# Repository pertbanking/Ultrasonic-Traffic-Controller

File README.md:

# Ultrasonic-Traffic-Controller
The Gay Atheist Club's Embedded System project repository.

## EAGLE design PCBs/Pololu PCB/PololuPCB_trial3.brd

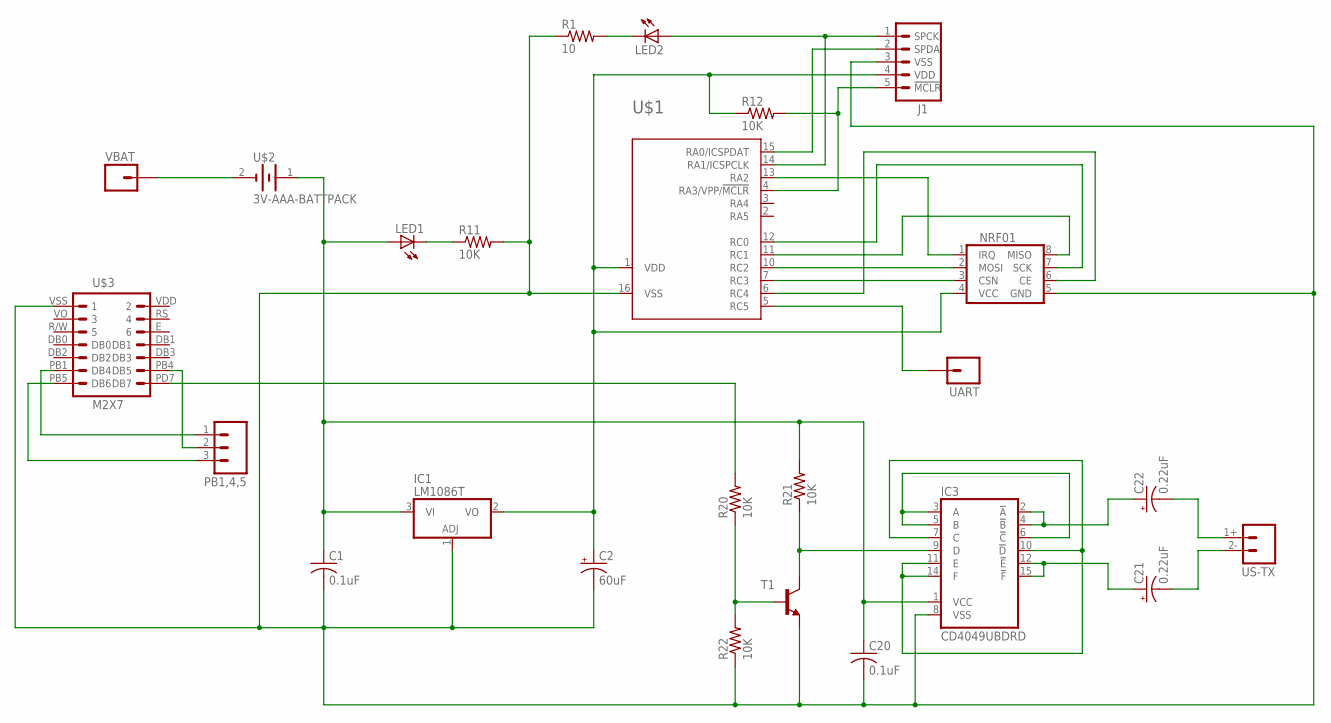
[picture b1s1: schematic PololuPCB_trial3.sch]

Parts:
C1, C20: 0.1uF; C0805
C2: 60uF; E2,5-5
C21, C22: 0.22uF; E2,5-6E
IC1: LM1086T; TO220H
IC3: CD4049UBDRD; SO16
J1: M05PTH; 1X05
LED1: LED5MM
LED2: LED_E; LED_1206
NRF01: NRF01; JP4Q
PB1,4,5: M03PTH; 1X03
R1: 10; R0805
R11, R12, R20, R21, R22: 10K; R0805
T1: -NPN-SOT23-EBC; SOT23-EBC
U$1: PIC16F1503(DIL16); DIL16
U$2: 3V-AAA-BATTPACK
U$3: M2X7; 2X07
UART: M01PTH_LONGPAD; 1X01_LONGPAD
US-TX: M02UT-1640K-TT-2-R; ULTRASONIC-PEIZO
VBAT: M01PTH_LONGPAD; 1X01_LONGPAD

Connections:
unnamed: IC3.9 (D), R21.1, T1.C
unnamed: R20.2, U$3.PD7 (DB7)
unnamed: IC3.7 (C), IC3.10 (!D), IC3.11 (E), IC3.14 (F)
unnamed: IC3.3 (A), IC3.5 (B), IC3.6 (!C)
unnamed: C22.+, IC3.2 (!A), IC3.4 (!B)
unnamed: C1.2, C2.-, C20.2, IC1.1 (ADJ), IC3.8 (VSS), J1.3 (VSS), NRF01.5 (GND), R1.1, R11.2, R22.1, T1.E, U$1.16 (VSS), U$3.VSS (1)
unnamed: C21.+, IC3.12 (!E), IC3.15 (!F)
unnamed: R20.1, R22.2, T1.B
unnamed: C2.+, IC1.2 (VO), J1.4 (VDD), NRF01.4 (VCC), R12.1, U$1.1 (VDD)
unnamed: LED2.C, R1.2
unnamed: NRF01.1 (IRQ), U$1.13 (RA2)
unnamed: NRF01.8 (MISO), U$1.11 (RC1)
unnamed: NRF01.3 (CSN), U$1.7 (RC3)
unnamed: NRF01.6 (CE), U$1.6 (RC4)
unnamed: NRF01.2 (MOSI), U$1.10 (RC2)
unnamed: NRF01.7 (SCK), U$1.12 (RC0)
unnamed: J1.2 (SPDA), U$1.15 (RA0/ICSPDAT)
unnamed: J1.1 (SPCK), LED2.A, U$1.14 (RA1/ICSPCLK)
unnamed: J1.5 (!MCLR), R12.2, U$1.4 (RA3/VPP/!MCLR)
unnamed: LED1.K (C), R11.1
unnamed: C22.-, US-TX.1+ (1)
unnamed: C21.-, US-TX.2- (2)
unnamed: C1.1, C20.1, IC1.3 (VI), IC3.1 (VCC), LED1.A, R21.2, U$2.1 (+)
unnamed: U$2.2 (-), VBAT.1
unnamed: U$1.5 (RC5), UART.1
unnamed: PB1,4,5.2, U$3.PB4 (DB5)
unnamed: PB1,4,5.1, U$3.PB1 (DB4)
unnamed: PB1,4,5.3, U$3.PB5 (DB6)

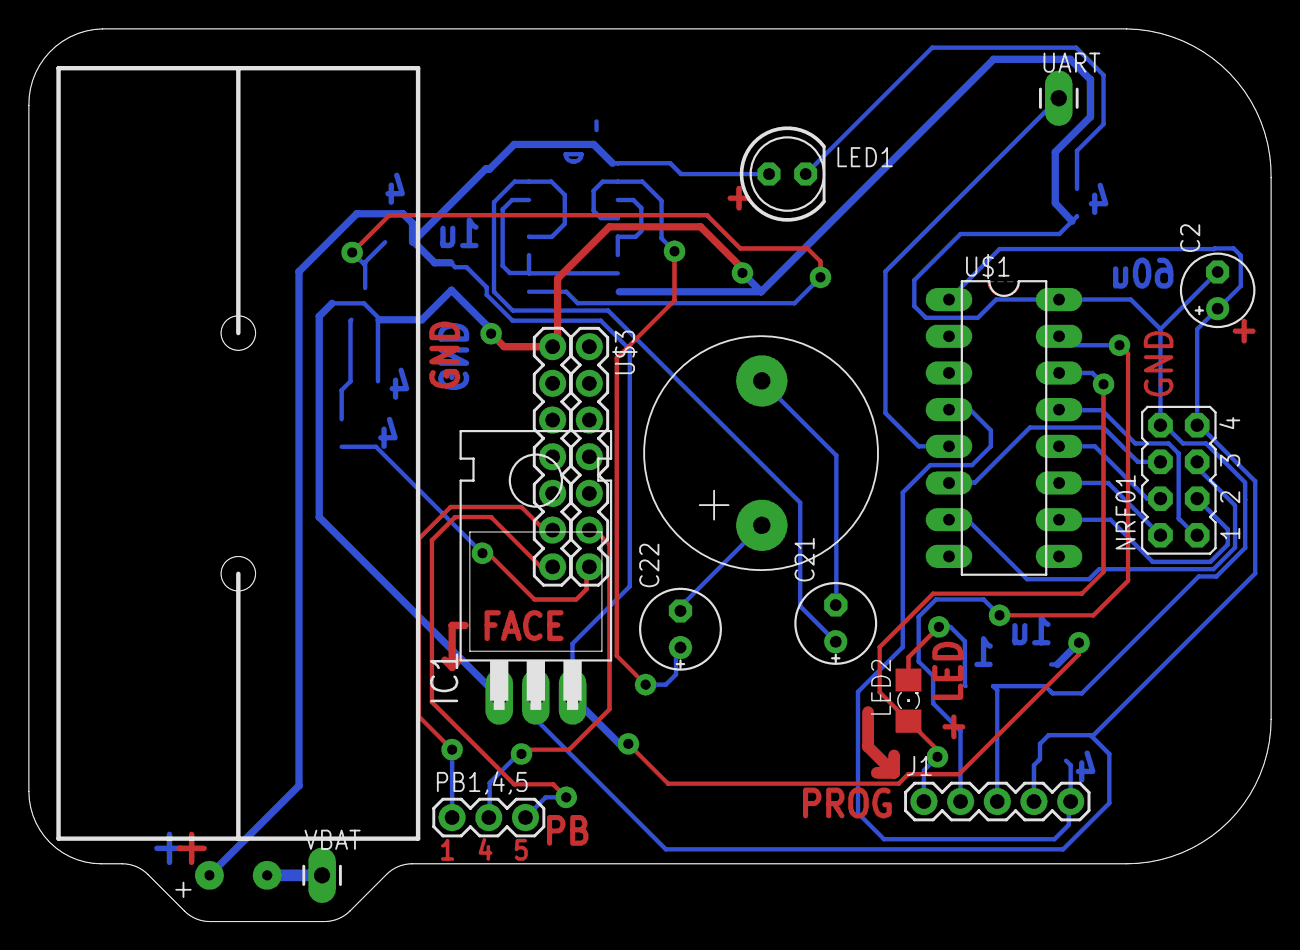
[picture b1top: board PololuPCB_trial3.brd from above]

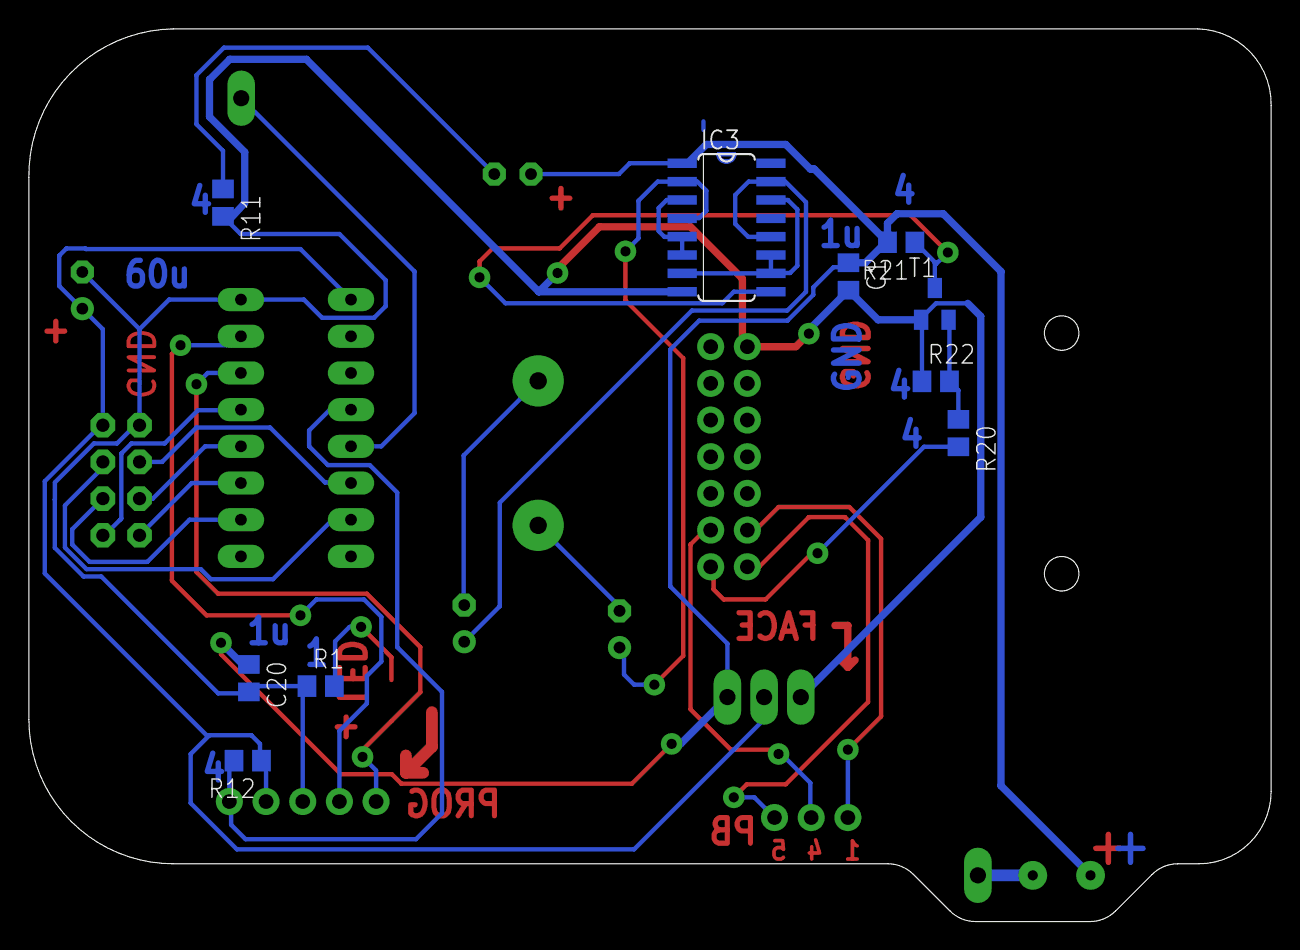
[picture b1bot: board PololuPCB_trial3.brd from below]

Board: 2 copper layers, 86.0 x 61.8 mm, 25 parts (10 on the bottom side), 28 nets.

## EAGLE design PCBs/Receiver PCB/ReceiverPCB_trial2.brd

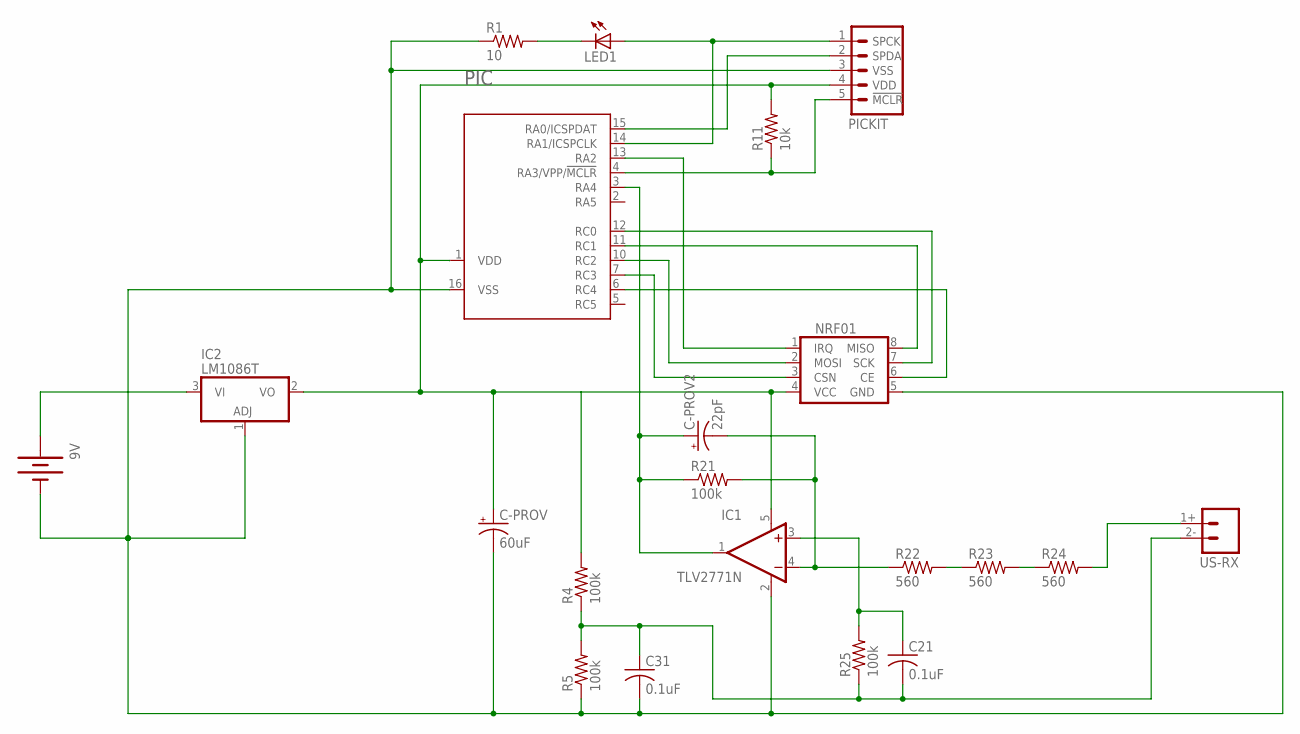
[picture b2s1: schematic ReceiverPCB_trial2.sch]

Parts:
9V: BATTERY9V; BATTCON_9V
C21, C31: 0.1uF; C0805
C-PROV: 60uF; E2,5-6E
C-PROV2: 22pF; E2,5-6E
IC1: TLV2771N; SOT23-5
IC2: LM1086T; TO220H
LED1: LED_E; LED_1206
NRF01: NRF01; JP4Q
PIC: PIC16F1503(DIL16); DIL16
PICKIT: M05PTH; 1X05
R1: 10; R0805
R4, R5, R21, R25: 100k; R0805
R11: 10k; R0805
R22, R23, R24: 560; R0805
US-RX: M02UT-1640K-TT-2-R; ULTRASONIC-PEIZO

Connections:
unnamed: LED1.A, PIC.14 (RA1/ICSPCLK), PICKIT.1 (SPCK)
unnamed: PIC.15 (RA0/ICSPDAT), PICKIT.2 (SPDA)
unnamed: LED1.C, R1.2
unnamed: C-PROV.+, IC1.5 (V+), IC2.2 (VO), NRF01.4 (VCC), PIC.1 (VDD), PICKIT.4 (VDD), R4.2, R11.2
unnamed: NRF01.1 (IRQ), PIC.13 (RA2)
unnamed: PIC.4 (RA3/VPP/!MCLR), PICKIT.5 (!MCLR), R11.1
unnamed: NRF01.8 (MISO), PIC.11 (RC1)
unnamed: NRF01.3 (CSN), PIC.7 (RC3)
unnamed: NRF01.2 (MOSI), PIC.10 (RC2)
unnamed: NRF01.7 (SCK), PIC.12 (RC0)
unnamed: NRF01.6 (CE), PIC.6 (RC4)
unnamed: 9V.-, C31.2, C-PROV.-, IC1.2 (V-), IC2.1 (ADJ), NRF01.5 (GND), PIC.16 (VSS), PICKIT.3 (VSS), R1.1, R5.1
unnamed: 9V.+, IC2.3 (VI)
unnamed: C-PROV2.+, IC1.1 (OUT), PIC.3 (RA4), R21.1
unnamed: R24.2, US-RX.1+ (1)
unnamed: R22.2, R23.1
unnamed: R23.2, R24.1
unnamed: C-PROV2.-, IC1.4 (-IN), R21.2, R22.1
unnamed: C21.2, C31.1, R4.1, R5.2, R25.1, US-RX.2- (2)
unnamed: C21.1, IC1.3 (+IN), R25.2

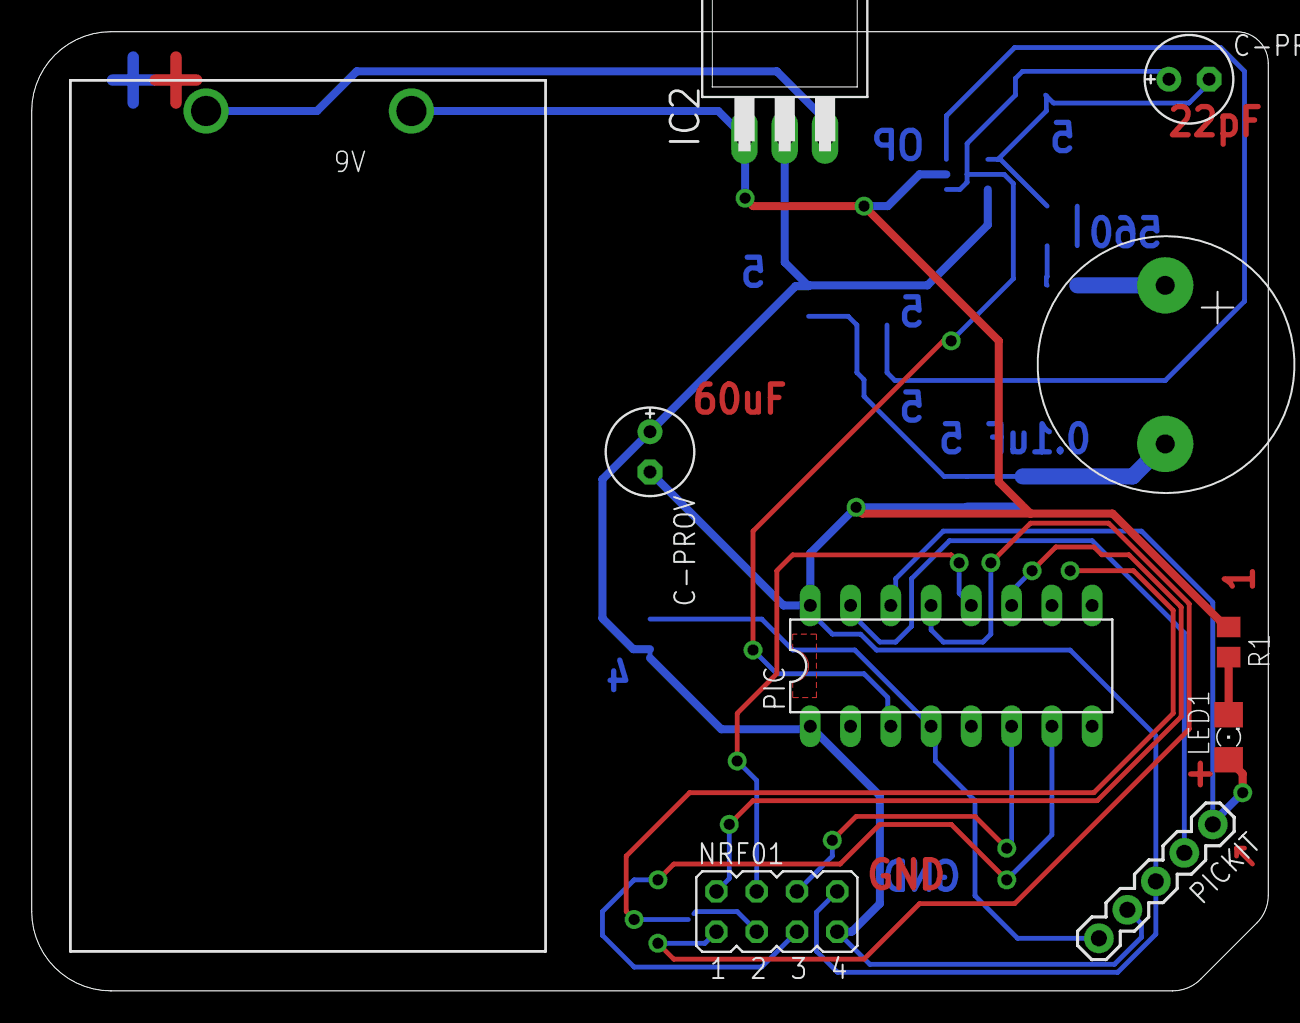
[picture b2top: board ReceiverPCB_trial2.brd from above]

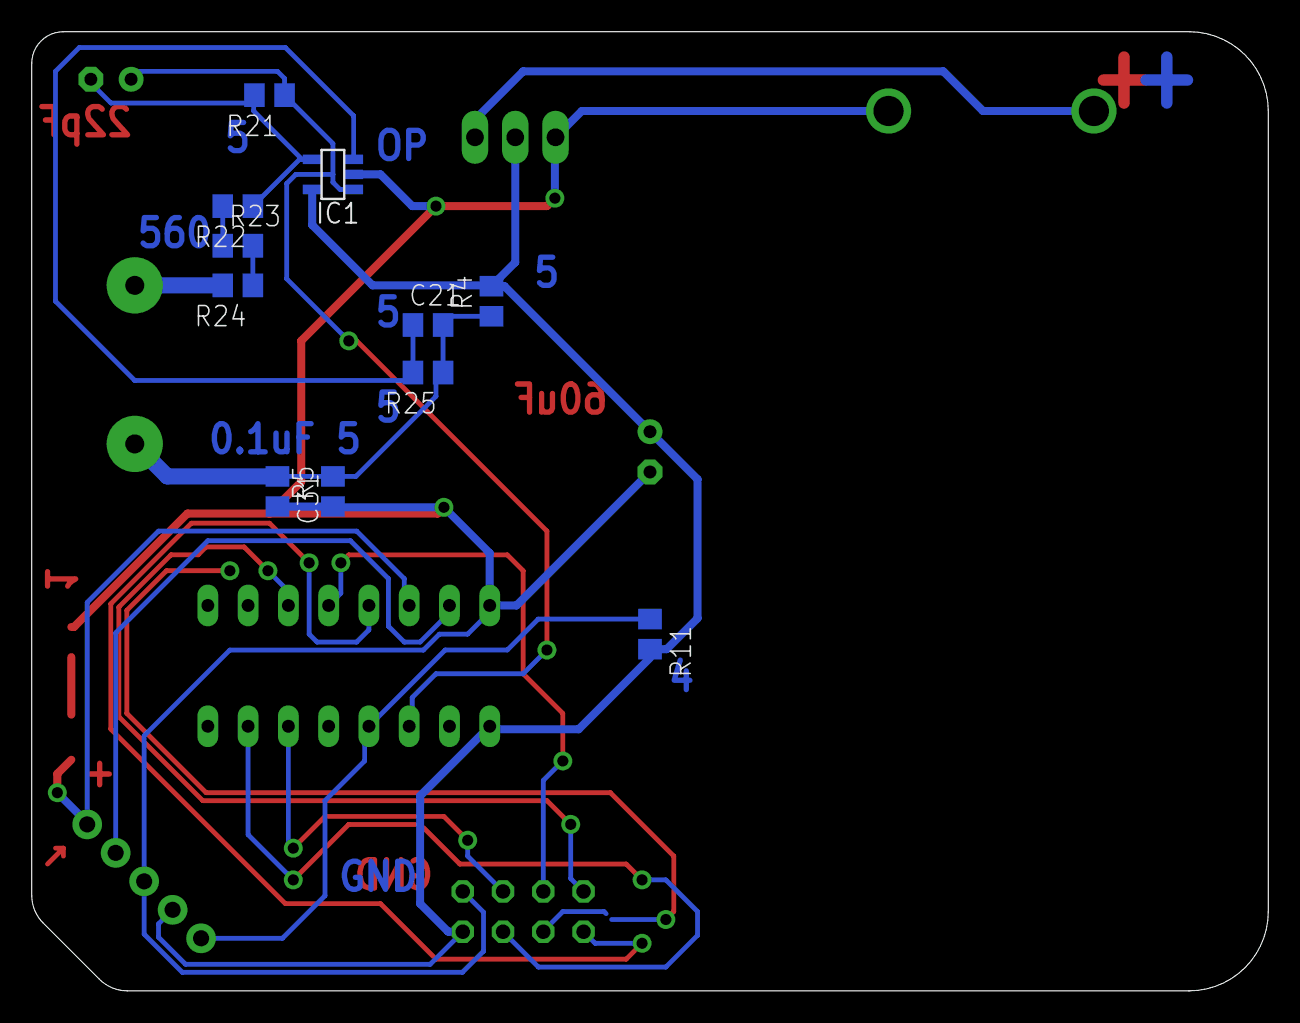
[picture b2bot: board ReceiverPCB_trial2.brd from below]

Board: 2 copper layers, 78.0 x 60.5 mm, 21 parts (11 on the bottom side), 20 nets.

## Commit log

2017-10-02 MSP asm code
    Added the ASM code for the MSP430 from TI
2017-11-10 added initial communications code for pic and avr
2017-11-10 bbb initial code for spi radio and bt module
2017-11-10 created bt .c and .h, need to move nrf code into .c and .h
2017-11-17 Wrote starter code for Pololu Ultrasound Xmit
    I don't know what I'm doing
2017-11-17 thanksgiving break update
2017-11-18 Added 3D Prints and PCBs folders
    Note that these files aren't always updated by me, so if you need to use them, make sure to tell me you're using them first! Then I'll give you the updated version
2017-11-20 Added cosmetic changes. See desc
    Push yer code boi. This stuff don't work yet. Replace it with code dat work.
2017-11-27 Set gitignore to ignore xml files
2017-11-27 Cleaned up 3D Print files
2017-11-27 latest bbb stuff
2017-11-27 newest pic stuff
2017-12-01 python simulation of avoidance
2017-12-01 IT KINDA WORKSgit add .git add .

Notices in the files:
parts and their libraries:
SparkFun-Connectors: Licensing: Creative Commons ShareAlike 4.0 International - https://creativecommons.org/licenses/by-sa/4.0
